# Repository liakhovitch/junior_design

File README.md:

# Digital Kitchen Timer
A project for ECE341 (Junior Design) class by Anton Liakhovitch

The system is based around an STM32f103 microcontoller.
Firmware is written in Rust, using the stm32f1xx_hal library and RTIC concurrency framework.

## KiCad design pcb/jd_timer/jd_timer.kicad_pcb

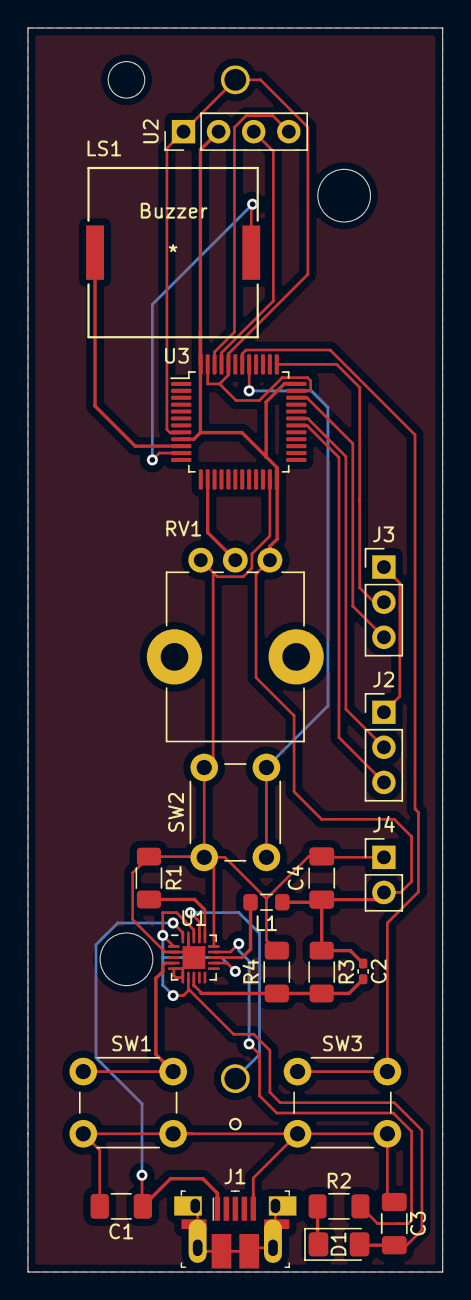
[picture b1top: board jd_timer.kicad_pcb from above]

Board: 2 copper layers, 30.0 x 90.0 mm, 23 parts (1 on the bottom side), 22 nets.

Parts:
BT1: Bat; 1043
C1, C3, C4: 10uF; C_1206_3216Metric_Pad1.33x1.80mm_HandSolder
C2: 10pF; C_0402_1005Metric_Pad0.74x0.62mm_HandSolder
D1: chg; LED_1206_3216Metric_Pad1.42x1.75mm_HandSolder
J1: 10103594-0001LF; USB_Micro_B_Female_10103594-0001LF
J2: Serial; PinHeader_1x03_P2.54mm_Vertical
J3: Debug; PinHeader_1x03_P2.54mm_Vertical
J4: Pwr; PinHeader_1x02_P2.54mm_Vertical
L1: 4.7uH; L_0805_2012Metric_Pad1.05x1.20mm_HandSolder
LS1: Buzzer; PKLCS1212E2000-R1
R1: 400R; R_1206_3216Metric_Pad1.30x1.75mm_HandSolder
R2: 160R; R_1206_3216Metric_Pad1.30x1.75mm_HandSolder
R3: 237k; R_1206_3216Metric_Pad1.30x1.75mm_HandSolder
R4: 75K; R_1206_3216Metric_Pad1.30x1.75mm_HandSolder
RV1: TIME_POT; Potentiometer_Bourns_PTV09A-1_Single_Vertical
SW1: PWR_BTN; SW_PUSH_6mm_H13mm
SW2: Start; SW_PUSH_6mm_H13mm
SW3: Brightness; SW_PUSH_6mm_H13mm
U1: LTC3553; QFN-20-1EP_3x3mm_P0.4mm_EP1.65x1.65mm
U2: oled_module; PinHeader_1x04_P2.54mm_Vertical
U3: STM32F103C8Tx; LQFP-48_7x7mm_P0.5mm

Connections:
3v3: C2.1, C4.1, J4.2, L1.1, R3.1, RV1.3, U2.2, U3.9, U3.24, U3.36, U3.48
/RX: J2.2, U3.31
/SWCLK: J3.2, U3.37
/SWDIO: J3.3, U3.34
/TX: J2.3, U3.30
GND: BT1.2, C1.2, C3.2, C4.2, J1.5, J2.1, J3.1, J4.1, R1.1, R4.2, RV1.1, SW1.1, SW2.1, SW3.1, U1.2, U1.5, U1.6, U1.15, U1.19, U1.21, U2.1, U3.8, U3.23, U3.35, U3.44, U3.47
unnamed: BT1.1, U1.17
unnamed: C1.1, J1.1, U1.20
unnamed: C2.2, R3.2, R4.1, U1.8
unnamed: D1.1, R2.1
unnamed: L1.2, U1.13
unnamed: LS1.1, U3.10
unnamed: LS1.2, U3.11
unnamed: R1.2, U1.16
unnamed: R2.2, U1.14
unnamed: RV1.2, U3.14
unnamed: SW1.2, U1.4
unnamed: SW2.2, U3.41
unnamed: SW3.2, U3.42
unnamed: U2.3, U3.45
unnamed: U2.4, U3.46
vout: C3.1, D1.2, U1.1, U1.7, U1.12, U1.18

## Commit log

2021-05-12 Finished PCB
2021-05-12 Init Rust project for jd timer
2021-05-12 Setup Rust project and got it to compile with basic RTIC application.
2021-05-12 Setup buttons (with interrupts) and ADC
2021-05-12 Added basic human input code
2021-05-23 Added UI handler code
2021-05-23 Added robustness to UI
2021-05-23 Added boot logo
2021-05-23 Implemented beep
2021-05-23 Added state switch task
2021-05-23 Added tick
2021-05-23 About to screw up some stuff
2021-05-24 idk man
2021-05-25 Commented references to RTC library.
2021-05-25 Reimplemented RTC library
2021-05-25 Got application mostly working. Todo: fix remaining bugs and add rtc calibration.
2021-05-26 Fixed bugs. Todo: RTC calibration
2021-05-26 Added RTC calibration
2021-05-26 Fixed some bugs and improved documentation
2021-05-27 Added charging indicator
2021-05-27 Added misc resources
2021-05-27 Removed build files. Oops.
2021-06-01 Added gitignore and CAD files
2021-06-01 Added readme file and images
2021-06-01 Added gcode to gitignore
2021-06-01 I think I finally got rid of those pesky gcode files
2021-06-12 Converted to rng firmware

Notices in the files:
parts and their libraries:
Copyright 2016 Accelerated Designs. All rights reserved.
